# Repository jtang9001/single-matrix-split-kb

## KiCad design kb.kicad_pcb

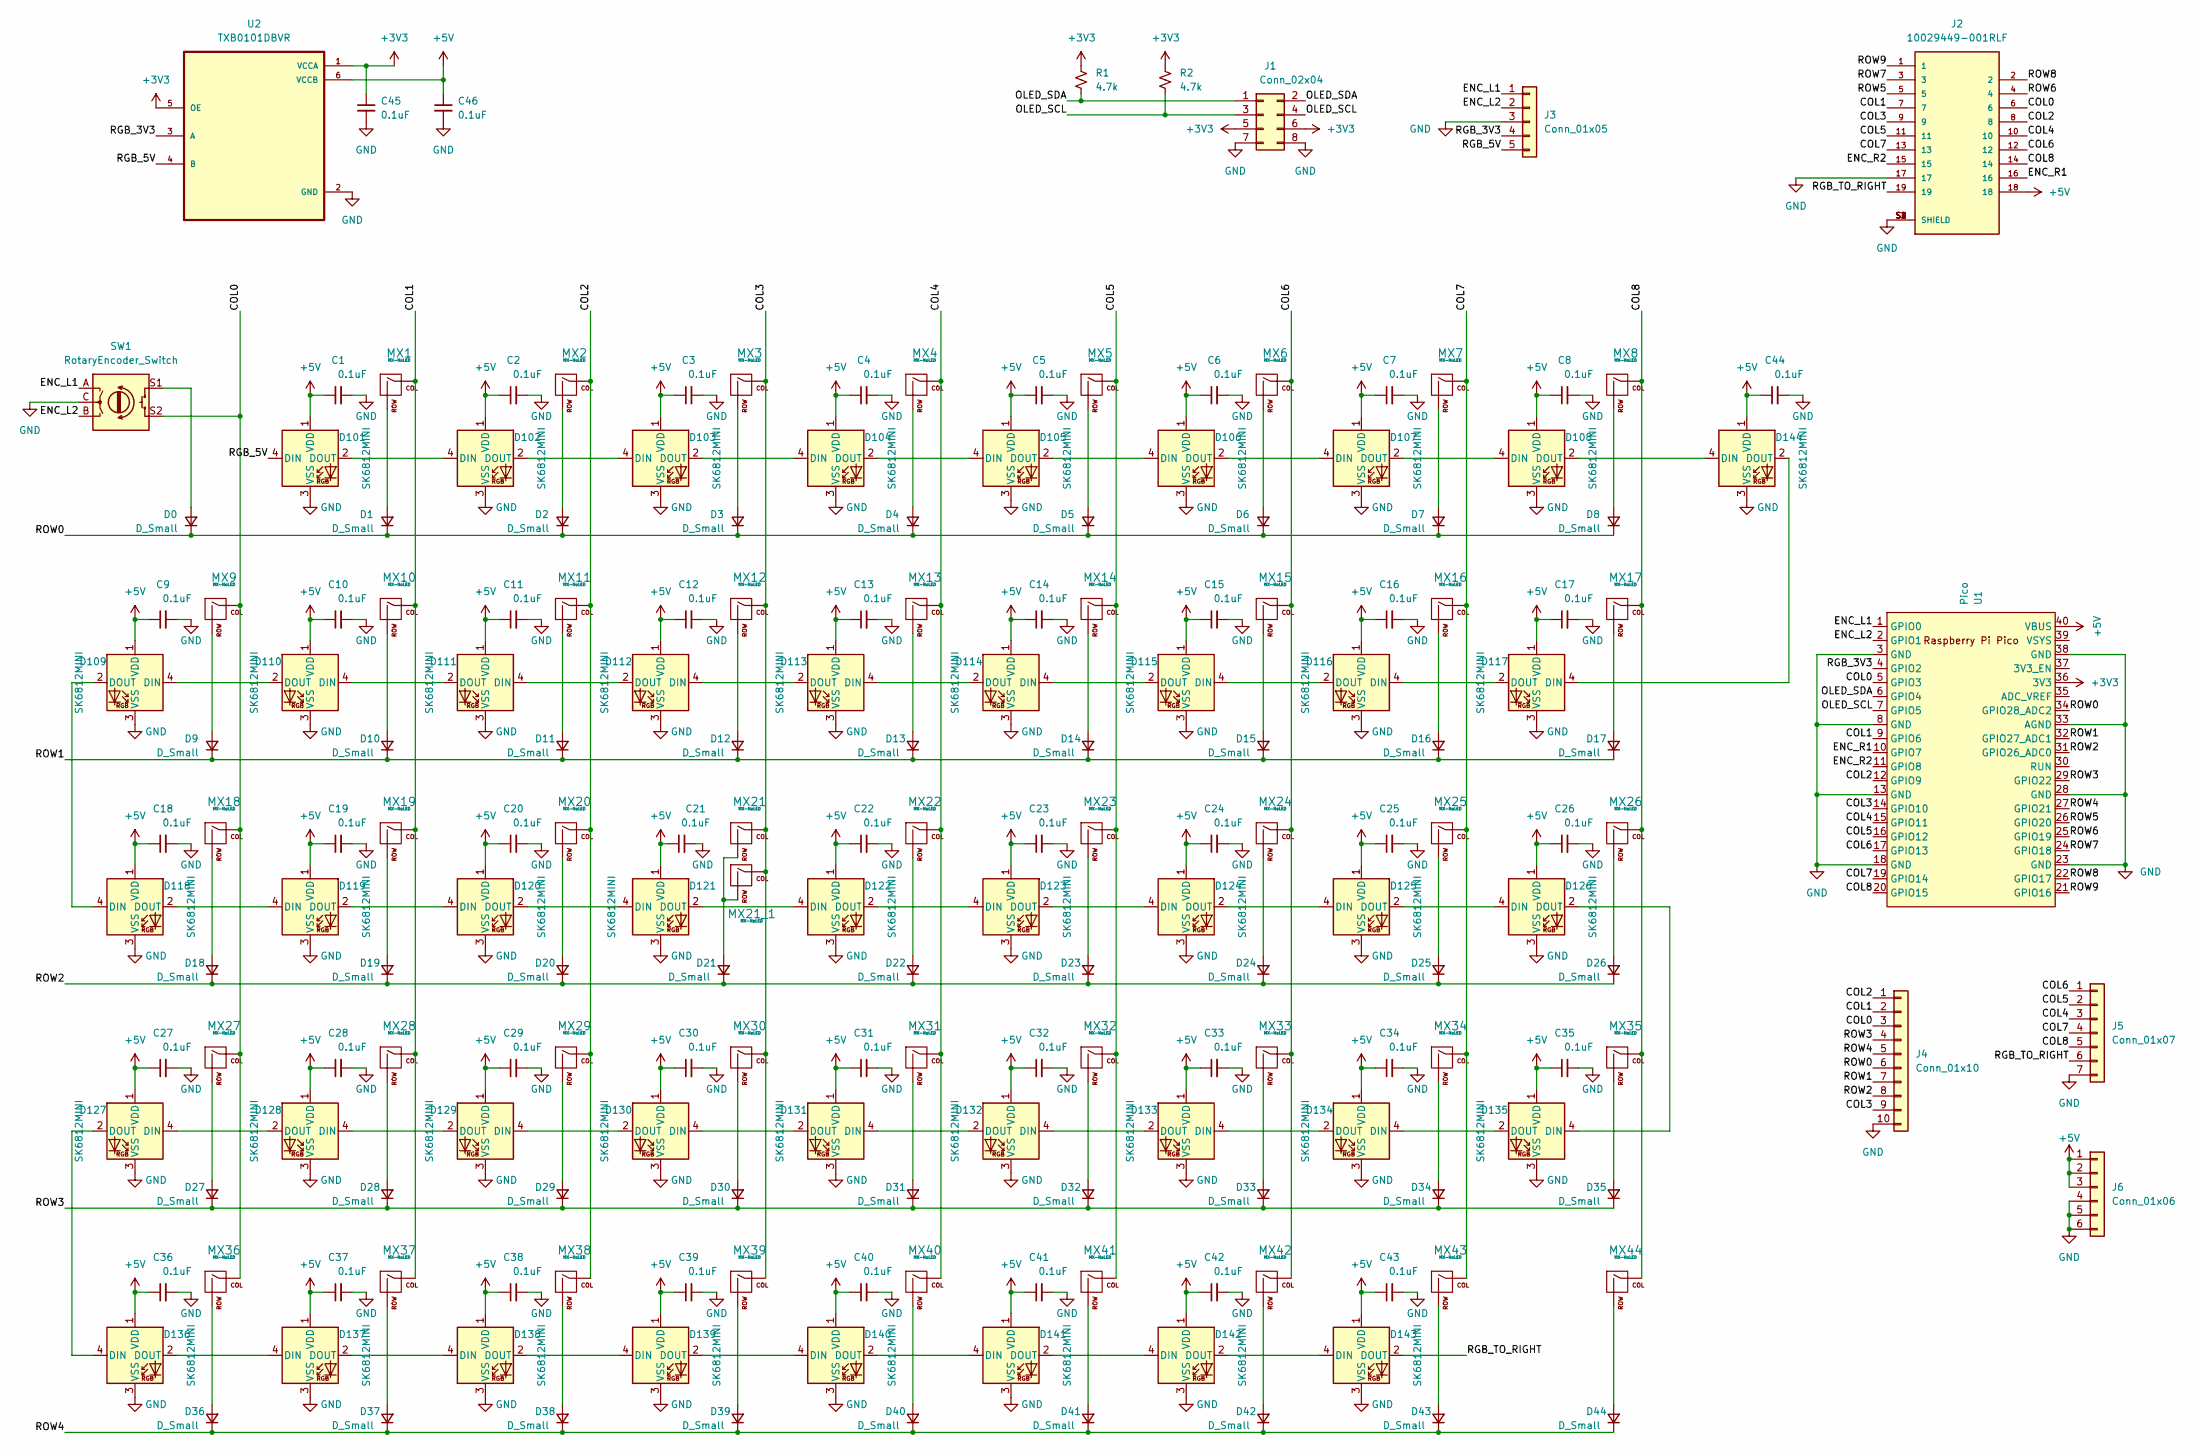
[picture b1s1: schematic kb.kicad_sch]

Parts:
C1, C2, C3, C4, C5, C6, C7, C8, C9, C10, C11, C12, C13, C14, C15, C16, C17, C18, C19, C20, C21, C22, C23, C24, C25, C26, C27, C28, C29, C30, C31, C32, C33, C34, C35, C36, C37, C38, C39, C40, C41, C42, C43, C44, C45, C46: 0.1uF; C_0805_2012Metric_Pad1.18x1.45mm_HandSolder
D0, D1, D2, D3, D4, D5, D6, D7, D8, D9, D10, D11, D12, D13, D14, D15, D16, D17, D18, D19, D20, D21, D22, D23, D24, D25, D26, D27, D28, D29, D30, D31, D32, D33, D34, D35, D36, D37, D38, D39, D40, D41, D42, D43, D44: D_Small; Diode-Hybrid-Back
D101, D102, D103, D104, D105, D106, D107, D108, D109, D110, D111, D112, D113, D114, D115, D116, D117, D118, D119, D120, D121, D122, D123, D124, D125, D126, D127, D128, D129, D130, D131, D132, D133, D134, D135, D136, D137, D138, D139, D140, D141, D142, D143, D144: SK6812MINI; SK6812-MINI-E
J1: Conn_02x04; PinHeader_2x04_P2.54mm_Vertical
J2: 10029449-001RLF; AMPHENOL_10029449-001RLF; PARTREV V
J3: Conn_01x05; PinHeader_1x05_P2.54mm_Vertical
J4: Conn_01x10; PinHeader_1x10_P2.54mm_Vertical
J5: Conn_01x07; PinHeader_1x07_P2.54mm_Vertical
J6: Conn_01x06; PinHeader_1x06_P2.54mm_Vertical
MX1, MX2, MX3, MX4, MX5, MX6, MX7, MX8, MX9, MX10, MX11, MX13, MX14, MX15, MX16, MX17, MX18, MX19, MX20, MX22, MX23, MX24, MX25, MX26, MX27, MX28, MX29, MX31, MX32, MX33, MX34, MX35, MX36, MX37, MX38, MX44: MX-NoLED; MXOnly-1U-Hotswap
MX12, MX39: MX-NoLED; MXOnly-1.5U-Hotswap
MX21: MX-NoLED; MXOnly-1.75U-Hotswap
MX21_1, MX40, MX41, MX42: MX-NoLED; MXOnly-1.25U-Hotswap
MX30: MX-NoLED; MXOnly-2.25U-Hotswap
MX43: MX-NoLED; MXOnly-2U-Hotswap-ReversedStabilizers
R1, R2: 4.7k; R_0805_2012Metric_Pad1.20x1.40mm_HandSolder
SW1: RotaryEncoder_Switch; RotaryEncoder_EC11
U1: Pico; RPi_Pico_SMD_TH
U2: TXB0101DBVR; SOT65P210X110-6N

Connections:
+3V3: C45.1, J1.5, J1.6, R1.1, R2.1, U1.36 (3V3), U2.1 (VCCA), U2.5 (OE)
+5V: C1.1, C2.1, C3.1, C4.1, C5.1, C6.1, C7.1, C8.1, C9.1, C10.1, C11.1, C12.1, C13.1, C14.1, C15.1, C16.1, C17.1, C18.1, C19.1, C20.1, C21.1, C22.1, C23.1, C24.1, C25.1, C26.1, C27.1, C28.1, C29.1, C30.1, C31.1, C32.1, C33.1, C34.1, C35.1, C36.1, C37.1, C38.1, C39.1, C40.1, C41.1, C42.1, C43.1, C44.1, C46.1, D101.1 (VDD), D102.1 (VDD), D103.1 (VDD), D104.1 (VDD), D105.1 (VDD), D106.1 (VDD), D107.1 (VDD), D108.1 (VDD), D109.1 (VDD), D110.1 (VDD), D111.1 (VDD), D112.1 (VDD), D113.1 (VDD), D114.1 (VDD), D115.1 (VDD), D116.1 (VDD), D117.1 (VDD), D118.1 (VDD), D119.1 (VDD), D120.1 (VDD), D121.1 (VDD), D122.1 (VDD), D123.1 (VDD), D124.1 (VDD), D125.1 (VDD), D126.1 (VDD), D127.1 (VDD), D128.1 (VDD), D129.1 (VDD), D130.1 (VDD), D131.1 (VDD), D132.1 (VDD), D133.1 (VDD), D134.1 (VDD), D135.1 (VDD), D136.1 (VDD), D137.1 (VDD), D138.1 (VDD), D139.1 (VDD), D140.1 (VDD), D141.1 (VDD), D142.1 (VDD), D143.1 (VDD), D144.1 (VDD), J2.18, J6.1, J6.2, J6.3, U1.40 (VBUS), U2.6 (VCCB)
/COL0: J2.6, J4.3, MX9.1 (COL), MX18.1 (COL), MX27.1 (COL), MX36.1 (COL), SW1.S2, U1.5 (GPIO3)
/COL1: J2.7, J4.2, MX1.1 (COL), MX10.1 (COL), MX19.1 (COL), MX28.1 (COL), MX37.1 (COL), U1.9 (GPIO6)
/COL2: J2.8, J4.1, MX2.1 (COL), MX11.1 (COL), MX20.1 (COL), MX29.1 (COL), MX38.1 (COL), U1.12 (GPIO9)
/COL3: J2.9, J4.9, MX3.1 (COL), MX12.1 (COL), MX21.1 (COL), MX21_1.1 (COL), MX30.1 (COL), MX39.1 (COL), U1.14 (GPIO10)
/COL4: J2.10, J5.3, MX4.1 (COL), MX13.1 (COL), MX22.1 (COL), MX31.1 (COL), MX40.1 (COL), U1.15 (GPIO11)
/COL5: J2.11, J5.2, MX5.1 (COL), MX14.1 (COL), MX23.1 (COL), MX32.1 (COL), MX41.1 (COL), U1.16 (GPIO12)
/COL6: J2.12, J5.1, MX6.1 (COL), MX15.1 (COL), MX24.1 (COL), MX33.1 (COL), MX42.1 (COL), U1.17 (GPIO13)
/COL7: J2.13, J5.4, MX7.1 (COL), MX16.1 (COL), MX25.1 (COL), MX34.1 (COL), MX43.1 (COL), U1.19 (GPIO14)
/COL8: J2.14, J5.5, MX8.1 (COL), MX17.1 (COL), MX26.1 (COL), MX35.1 (COL), MX44.1 (COL), U1.20 (GPIO15)
/ENC_L1: J3.1, SW1.A, U1.1 (GPIO0)
/ENC_L2: J3.2, SW1.B, U1.2 (GPIO1)
/ENC_R1: J2.16, U1.10 (GPIO7)
/ENC_R2: J2.15, U1.11 (GPIO8)
/OLED_SCL: J1.3, J1.4, R2.2, U1.7 (GPIO5)
/OLED_SDA: J1.1, J1.2, R1.2, U1.6 (GPIO4)
/RGB_3V3: J3.4, U1.4 (GPIO2), U2.3 (A)
/RGB_5V: D101.4 (DIN), J3.5, U2.4 (B)
/RGB_TO_RIGHT: D143.2 (DOUT), J2.19, J5.6
/ROW0: D0.1 (K), D1.1 (K), D2.1 (K), D3.1 (K), D4.1 (K), D5.1 (K), D6.1 (K), D7.1 (K), D8.1 (K), J4.6, U1.34 (GPIO28_ADC2)
/ROW1: D9.1 (K), D10.1 (K), D11.1 (K), D12.1 (K), D13.1 (K), D14.1 (K), D15.1 (K), D16.1 (K), D17.1 (K), J4.7, U1.32 (GPIO27_ADC1)
/ROW2: D18.1 (K), D19.1 (K), D20.1 (K), D21.1 (K), D22.1 (K), D23.1 (K), D24.1 (K), D25.1 (K), D26.1 (K), J4.8, U1.31 (GPIO26_ADC0)
/ROW3: D27.1 (K), D28.1 (K), D29.1 (K), D30.1 (K), D31.1 (K), D32.1 (K), D33.1 (K), D34.1 (K), D35.1 (K), J4.4, U1.29 (GPIO22)
/ROW4: D36.1 (K), D37.1 (K), D38.1 (K), D39.1 (K), D40.1 (K), D41.1 (K), D42.1 (K), D43.1 (K), D44.1 (K), J4.5, U1.27 (GPIO21)
/ROW5: J2.5, U1.26 (GPIO20)
/ROW6: J2.4, U1.25 (GPIO19)
/ROW7: J2.3, U1.24 (GPIO18)
/ROW8: J2.2, U1.22 (GPIO17)
/ROW9: J2.1, U1.21 (GPIO16)
GND: C1.2, C2.2, C3.2, C4.2, C5.2, C6.2, C7.2, C8.2, C9.2, C10.2, C11.2, C12.2, C13.2, C14.2, C15.2, C16.2, C17.2, C18.2, C19.2, C20.2, C21.2, C22.2, C23.2, C24.2, C25.2, C26.2, C27.2, C28.2, C29.2, C30.2, C31.2, C32.2, C33.2, C34.2, C35.2, C36.2, C37.2, C38.2, C39.2, C40.2, C41.2, C42.2, C43.2, C44.2, C45.2, C46.2, D101.3 (VSS), D102.3 (VSS), D103.3 (VSS), D104.3 (VSS), D105.3 (VSS), D106.3 (VSS), D107.3 (VSS), D108.3 (VSS), D109.3 (VSS), D110.3 (VSS), D111.3 (VSS), D112.3 (VSS), D113.3 (VSS), D114.3 (VSS), D115.3 (VSS), D116.3 (VSS), D117.3 (VSS), D118.3 (VSS), D119.3 (VSS), D120.3 (VSS), D121.3 (VSS), D122.3 (VSS), D123.3 (VSS), D124.3 (VSS), D125.3 (VSS), D126.3 (VSS), D127.3 (VSS), D128.3 (VSS), D129.3 (VSS), D130.3 (VSS), D131.3 (VSS), D132.3 (VSS), D133.3 (VSS), D134.3 (VSS), D135.3 (VSS), D136.3 (VSS), D137.3 (VSS), D138.3 (VSS), D139.3 (VSS), D140.3 (VSS), D141.3 (VSS), D142.3 (VSS), D143.3 (VSS), D144.3 (VSS), J1.7, J1.8, J2.17, J2.S1 (SHIELD), J2.S2 (SHIELD), J2.S3 (SHIELD), J2.S4 (SHIELD), J3.3, J4.10, J5.7, J6.4, J6.5, J6.6, SW1.C, U1.3 (GND), U1.8 (GND), U1.13 (GND), U1.18 (GND), U1.23 (GND), U1.28 (GND), U1.33 (AGND), U1.38 (GND), U2.2 (GND)
unnamed: D0.2 (A), SW1.S1
unnamed: D1.2 (A), MX1.2 (ROW)
unnamed: D2.2 (A), MX2.2 (ROW)
unnamed: D3.2 (A), MX3.2 (ROW)
unnamed: D4.2 (A), MX4.2 (ROW)
unnamed: D5.2 (A), MX5.2 (ROW)
unnamed: D6.2 (A), MX6.2 (ROW)
unnamed: D7.2 (A), MX7.2 (ROW)
unnamed: D8.2 (A), MX8.2 (ROW)
unnamed: D9.2 (A), MX9.2 (ROW)
unnamed: D10.2 (A), MX10.2 (ROW)
unnamed: D11.2 (A), MX11.2 (ROW)
unnamed: D12.2 (A), MX12.2 (ROW)
unnamed: D13.2 (A), MX13.2 (ROW)
unnamed: D14.2 (A), MX14.2 (ROW)
unnamed: D15.2 (A), MX15.2 (ROW)
unnamed: D16.2 (A), MX16.2 (ROW)
unnamed: D17.2 (A), MX17.2 (ROW)
unnamed: D18.2 (A), MX18.2 (ROW)
unnamed: D19.2 (A), MX19.2 (ROW)
unnamed: D20.2 (A), MX20.2 (ROW)
unnamed: D21.2 (A), MX21.2 (ROW), MX21_1.2 (ROW)
unnamed: D22.2 (A), MX22.2 (ROW)
unnamed: D23.2 (A), MX23.2 (ROW)
unnamed: D24.2 (A), MX24.2 (ROW)
unnamed: D25.2 (A), MX25.2 (ROW)
unnamed: D26.2 (A), MX26.2 (ROW)
unnamed: D27.2 (A), MX27.2 (ROW)
unnamed: D28.2 (A), MX28.2 (ROW)
unnamed: D29.2 (A), MX29.2 (ROW)
unnamed: D30.2 (A), MX30.2 (ROW)
unnamed: D31.2 (A), MX31.2 (ROW)
unnamed: D32.2 (A), MX32.2 (ROW)
unnamed: D33.2 (A), MX33.2 (ROW)
unnamed: D34.2 (A), MX34.2 (ROW)
unnamed: D35.2 (A), MX35.2 (ROW)
unnamed: D36.2 (A), MX36.2 (ROW)
unnamed: D37.2 (A), MX37.2 (ROW)
unnamed: D38.2 (A), MX38.2 (ROW)
unnamed: D39.2 (A), MX39.2 (ROW)
unnamed: D40.2 (A), MX40.2 (ROW)
unnamed: D41.2 (A), MX41.2 (ROW)
unnamed: D42.2 (A), MX42.2 (ROW)
unnamed: D43.2 (A), MX43.2 (ROW)
unnamed: D44.2 (A), MX44.2 (ROW)
unnamed: D101.2 (DOUT), D102.4 (DIN)
unnamed: D102.2 (DOUT), D103.4 (DIN)
unnamed: D103.2 (DOUT), D104.4 (DIN)
unnamed: D104.2 (DOUT), D105.4 (DIN)
unnamed: D105.2 (DOUT), D106.4 (DIN)
unnamed: D106.2 (DOUT), D107.4 (DIN)
unnamed: D107.2 (DOUT), D108.4 (DIN)
unnamed: D108.2 (DOUT), D144.4 (DIN)
unnamed: D109.4 (DIN), D110.2 (DOUT)
unnamed: D110.4 (DIN), D111.2 (DOUT)
unnamed: D111.4 (DIN), D112.2 (DOUT)
unnamed: D112.4 (DIN), D113.2 (DOUT)
unnamed: D113.4 (DIN), D114.2 (DOUT)
unnamed: D114.4 (DIN), D115.2 (DOUT)
unnamed: D115.4 (DIN), D116.2 (DOUT)
unnamed: D116.4 (DIN), D117.2 (DOUT)
unnamed: D118.2 (DOUT), D119.4 (DIN)
unnamed: D109.2 (DOUT), D118.4 (DIN)
unnamed: D119.2 (DOUT), D120.4 (DIN)
unnamed: D120.2 (DOUT), D121.4 (DIN)
unnamed: D121.2 (DOUT), D122.4 (DIN)
unnamed: D122.2 (DOUT), D123.4 (DIN)
unnamed: D123.2 (DOUT), D124.4 (DIN)
unnamed: D124.2 (DOUT), D125.4 (DIN)
unnamed: D125.2 (DOUT), D126.4 (DIN)
unnamed: D126.2 (DOUT), D135.4 (DIN)
unnamed: D127.4 (DIN), D128.2 (DOUT)
unnamed: D128.4 (DIN), D129.2 (DOUT)
unnamed: D129.4 (DIN), D130.2 (DOUT)
unnamed: D130.4 (DIN), D131.2 (DOUT)
unnamed: D131.4 (DIN), D132.2 (DOUT)
unnamed: D132.4 (DIN), D133.2 (DOUT)
unnamed: D133.4 (DIN), D134.2 (DOUT)
unnamed: D134.4 (DIN), D135.2 (DOUT)
unnamed: D136.2 (DOUT), D137.4 (DIN)
unnamed: D127.2 (DOUT), D136.4 (DIN)
unnamed: D137.2 (DOUT), D138.4 (DIN)
unnamed: D138.2 (DOUT), D139.4 (DIN)
unnamed: D139.2 (DOUT), D140.4 (DIN)
unnamed: D140.2 (DOUT), D141.4 (DIN)
unnamed: D141.2 (DOUT), D142.4 (DIN)
unnamed: D142.2 (DOUT), D143.4 (DIN)
unnamed: D117.4 (DIN), D144.2 (DOUT)

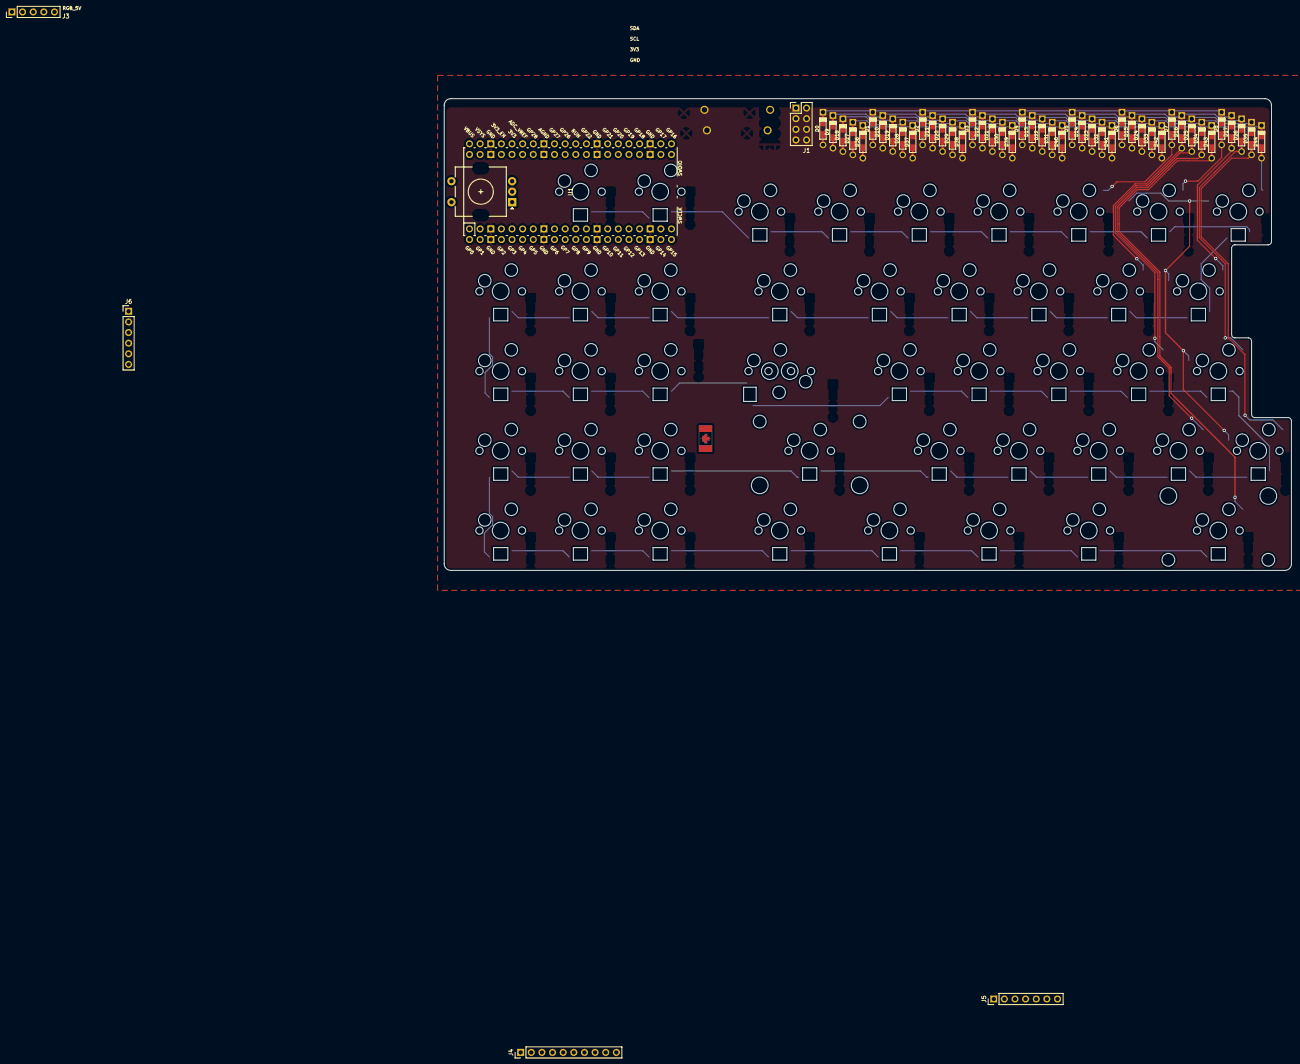
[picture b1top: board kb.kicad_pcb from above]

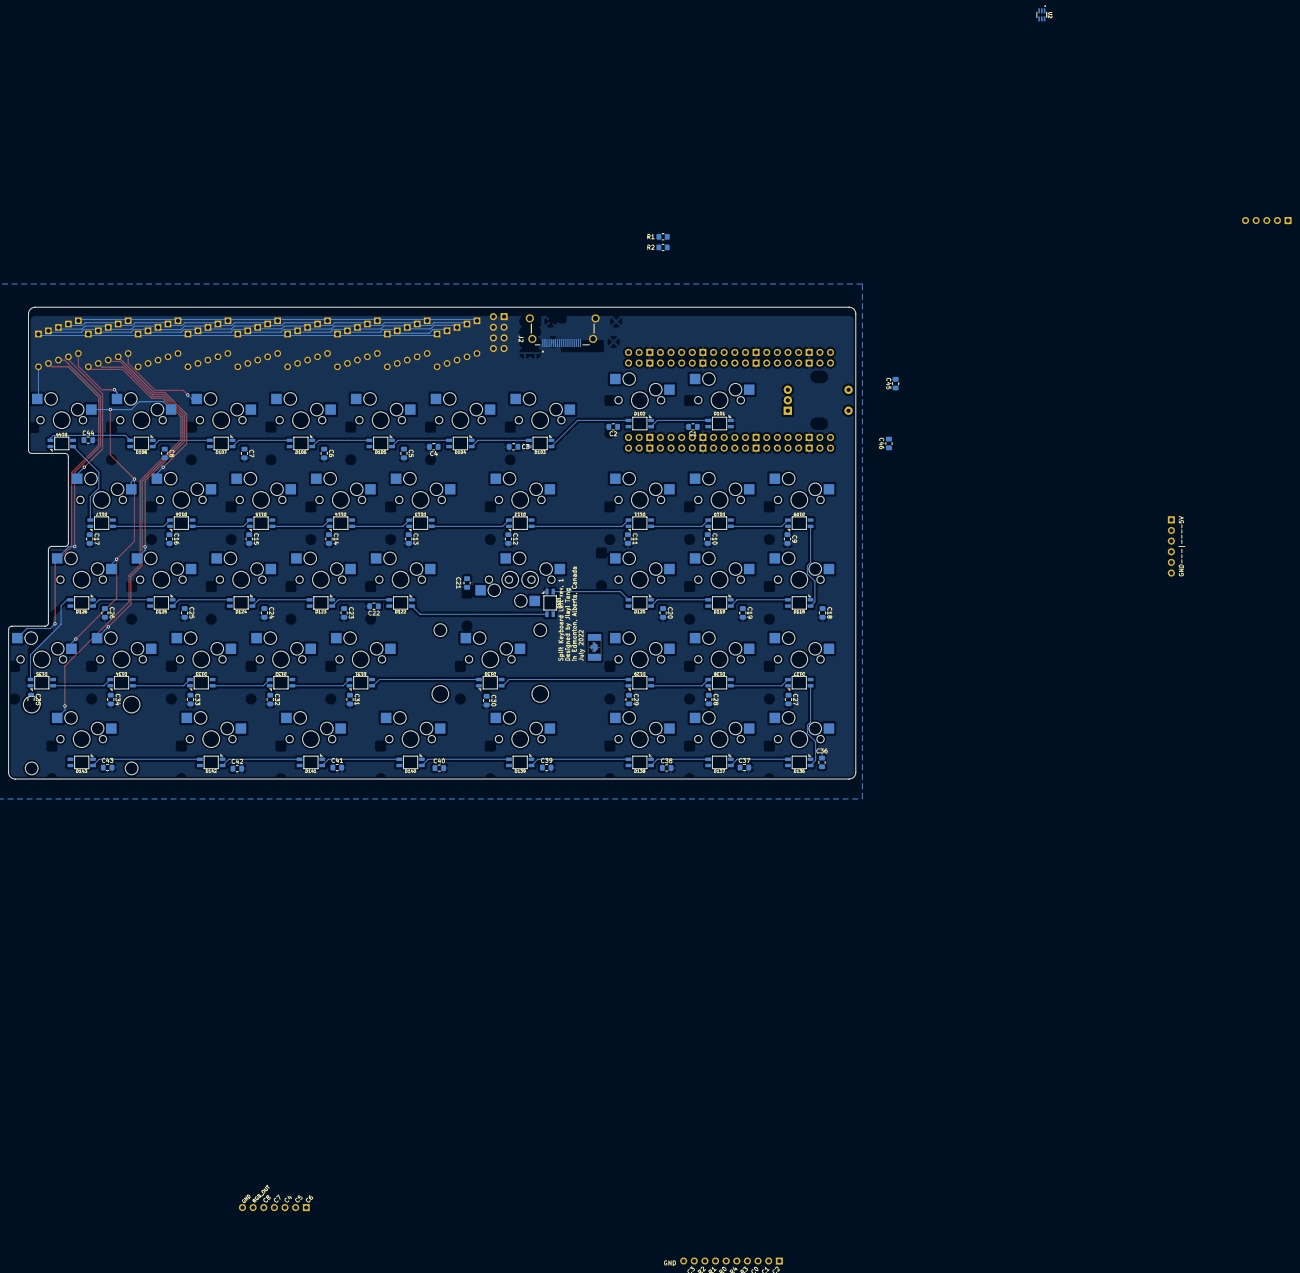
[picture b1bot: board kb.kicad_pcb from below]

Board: 2 copper layers, 202.4 x 112.7 mm, 191 parts (139 on the bottom side), 119 nets.

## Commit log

2022-07-08 started project
2022-07-08 add keebio library
2022-07-08 add library?
2022-07-08 selected libraries
2022-07-08 added rpi pico library
2022-07-08 submitted rpi pico libraries?
2022-07-08 confirmed rp2040 schematic working
2022-07-08 started putting down symbols for matrix
2022-07-09 started labelling nets
2022-07-09 added footprints
2022-07-09 fixed diode designators
2022-07-09 laid out LEDs
2022-07-09 layout nearly finished
2022-07-09 about to start routing
2022-07-10 cols 3-8 done
2022-07-10 before rgb restructure
2022-07-10 relaying out?
2022-07-10 fixing sk6812s
2022-07-11 routing hdmi done
2022-07-11 finished routing!
2022-07-11 add 3d model
2022-07-11 added 3d models
2022-07-11 3d model complete
2022-07-14 start adding test points
2022-07-14 Added test points
2022-07-14 added silkscreen labels
2022-07-14 add silkscreens, power port
2022-07-14 Add signature :)
2022-07-14 Add pullup i2c
2022-07-14 shift hdmi board cutout
2022-07-14 add new level shifter, add component values
2022-07-14 changed footprints
2022-07-14 fix component values
2022-07-16 added stepped capslock support
2022-07-17 before branching for through-hole version
2022-07-17 start routing thru hole version
2022-07-18 routing rough draft
2022-07-18 started routing columns neatly
2022-07-18 more routing
2022-07-18 all wired up??
2022-07-19 finished routing?45 deg hdmi
2022-07-20 reduce to 4 arrays of key-spaced diodes
2022-07-20 finish routing 4x5 diodes
2022-07-20 add via stitching
2022-07-21 fixed through hole vias :(
2022-07-21 attempting PCB art
2022-07-22 way too many silkscreen tries lol
2022-07-26 update flag?
2022-07-26 flag checked
2022-07-26 sch, pcb checked
2022-07-27 add sideways encoder support
2022-07-27 Add right encoder filtering
2022-07-27 revise enc filter layout
2022-07-28 reroute enc filter
2022-07-28 add rgb out pinout
2022-07-28 add step file
2022-07-28 checked rules
2022-07-29 before final check??
2022-07-29 before sending to jlc
2022-07-29 after cad check
2022-07-30 version sent to jlc
2022-07-30 eod jul 29
